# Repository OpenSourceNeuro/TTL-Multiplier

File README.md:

# TTL-Multiplier
a simple rack-mounted hardware to multiple a 5V TTL signal without depleting the current source

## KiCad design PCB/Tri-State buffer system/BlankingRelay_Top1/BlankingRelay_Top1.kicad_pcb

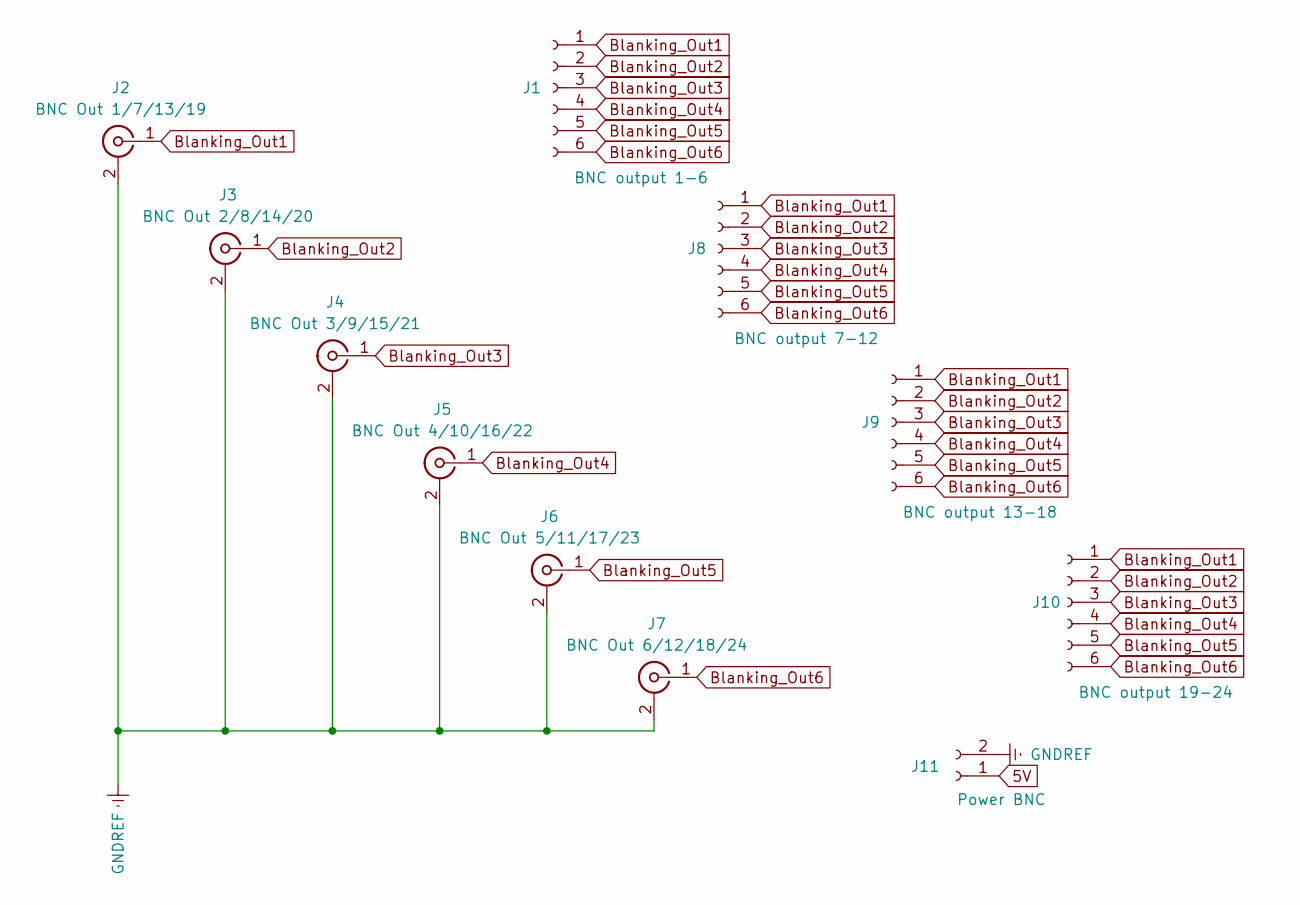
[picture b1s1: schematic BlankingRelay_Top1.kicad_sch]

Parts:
J1: BNC output 1-6; JST_XH_B6B-XH-A_1x06_P2.50mm_Vertical
J2: BNC Out 1/7/13/19; BNC_Socket_TYCO-AMP_LargePads
J3: BNC Out 2/8/14/20; BNC_Socket_TYCO-AMP_LargePads
J4: BNC Out 3/9/15/21; BNC_Socket_TYCO-AMP_LargePads
J5: BNC Out 4/10/16/22; BNC_Socket_TYCO-AMP_LargePads
J6: BNC Out 5/11/17/23; BNC_Socket_TYCO-AMP_LargePads
J7: BNC Out 6/12/18/24; BNC_Socket_TYCO-AMP_LargePads
J8: BNC output 7-12; JST_XH_B6B-XH-A_1x06_P2.50mm_Vertical
J9: BNC output 13-18; JST_XH_B6B-XH-A_1x06_P2.50mm_Vertical
J10: BNC output 19-24; JST_XH_B6B-XH-A_1x06_P2.50mm_Vertical
J11: Power BNC; JST_XH_B2B-XH-A_1x02_P2.50mm_Vertical

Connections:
5V: J11.1
Blanking_Out1: J1.1, J2.1 (In), J8.1, J9.1, J10.1
Blanking_Out2: J1.2, J3.1 (In), J8.2, J9.2, J10.2
Blanking_Out3: J1.3, J4.1 (In), J8.3, J9.3, J10.3
Blanking_Out4: J1.4, J5.1 (In), J8.4, J9.4, J10.4
Blanking_Out5: J1.5, J6.1 (In), J8.5, J9.5, J10.5
Blanking_Out6: J1.6, J7.1 (In), J8.6, J9.6, J10.6
GNDREF: J2.2 (Ext), J3.2 (Ext), J4.2 (Ext), J5.2 (Ext), J6.2 (Ext), J7.2 (Ext), J11.2

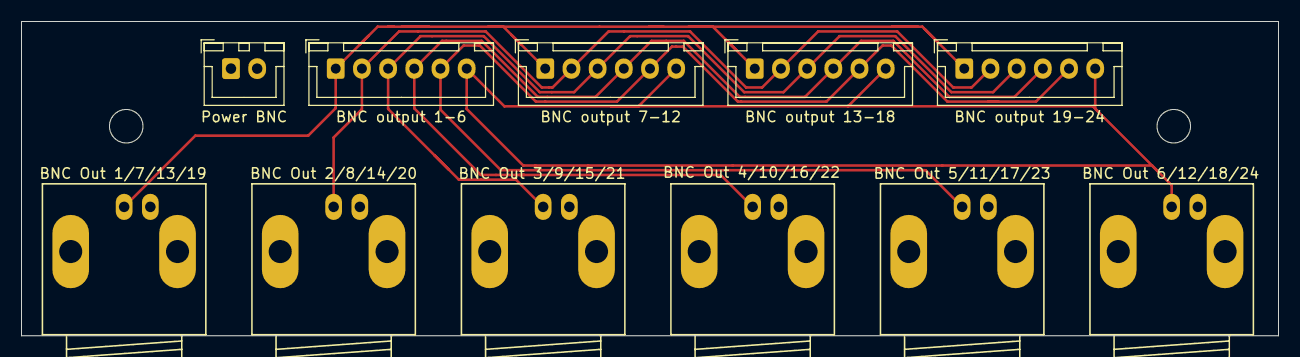
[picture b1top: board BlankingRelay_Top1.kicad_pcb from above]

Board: 2 copper layers, 120.0 x 30.0 mm, 11 parts (0 on the bottom side), 7 nets.

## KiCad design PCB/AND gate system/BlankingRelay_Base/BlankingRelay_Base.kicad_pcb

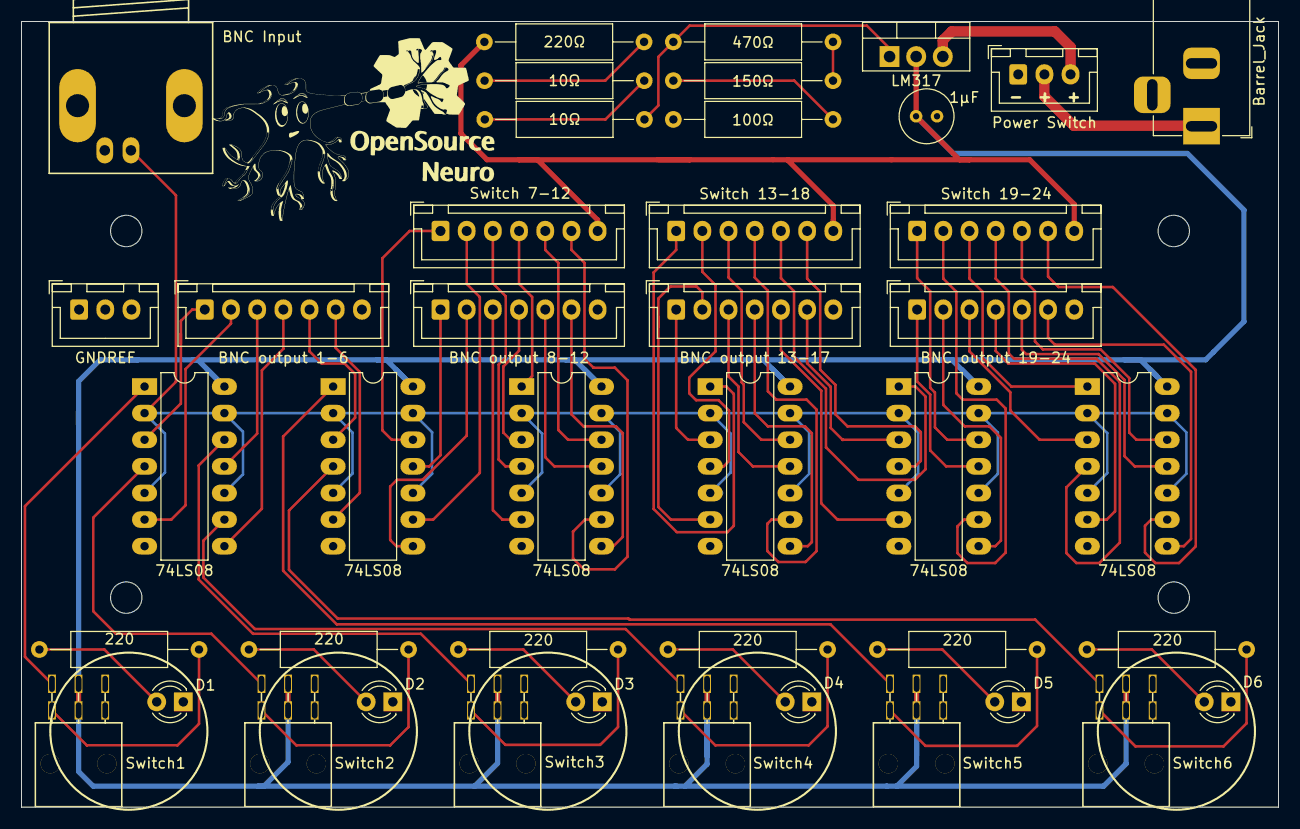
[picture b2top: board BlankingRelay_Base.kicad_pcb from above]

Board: 2 copper layers, 120.0 x 75.0 mm, 47 parts (0 on the bottom side), 70 nets.

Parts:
C1: 1μF; C_Radial_D5.0mm_H5.0mm_P2.00mm
D1, D2, D3, D4, D5, D6: LED; LED_D3.0mm
H1, H2, H3, H4: MountingHole; MountingHole_3mm
J1: Power Switch; JST_XH_B3B-XH-A_1x03_P2.50mm_Vertical
J2: BNC Input; BNC_Socket_TYCO-AMP_LargePads
J3: BNC output 1-6; JST_XH_B7B-XH-A_1x07_P2.50mm_Vertical
J4: BNC output 8-12; JST_XH_B7B-XH-A_1x07_P2.50mm_Vertical
J5: Switch 7-12; JST_XH_B7B-XH-A_1x07_P2.50mm_Vertical
J6: BNC output 13-17; JST_XH_B7B-XH-A_1x07_P2.50mm_Vertical
J7: Switch 13-18; JST_XH_B7B-XH-A_1x07_P2.50mm_Vertical
J8: BNC output 19-24; JST_XH_B7B-XH-A_1x07_P2.50mm_Vertical
J9: Switch 19-24; JST_XH_B7B-XH-A_1x07_P2.50mm_Vertical
J10: Barrel_Jack; BarrelJack_Horizontal
J11: GNDREF; JST_XH_B3B-XH-A_1x03_P2.50mm_Vertical
R1, R2, R3, R4, R5, R6: 220; R_Axial_DIN0309_L9.0mm_D3.2mm_P15.24mm_Horizontal
R7: 470Ω; R_Axial_DIN0309_L9.0mm_D3.2mm_P15.24mm_Horizontal
R8, R10: 10Ω; R_Axial_DIN0309_L9.0mm_D3.2mm_P15.24mm_Horizontal
R9: 150Ω; R_Axial_DIN0309_L9.0mm_D3.2mm_P15.24mm_Horizontal
R11: 100Ω; R_Axial_DIN0309_L9.0mm_D3.2mm_P15.24mm_Horizontal
R12: 220Ω; R_Axial_DIN0309_L9.0mm_D3.2mm_P15.24mm_Horizontal
Switch1, Switch2, Switch3, Switch4, Switch5, Switch6: SW_Push_DPDT; maxi_DPDT_Angled
U1, U2, U3, U4, U5, U6: 74LS08; DIP-14_W7.62mm_LongPads
U7: LM317; TO-220-3_Vertical

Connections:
5V: C1.1, J5.7, J7.7, J9.7, R12.1, Switch1.2 (B), Switch1.5 (B), Switch2.2 (B), Switch2.5 (B), Switch3.2 (B), Switch3.5 (B), Switch4.2 (B), Switch4.5 (B), Switch5.2 (B), Switch5.5 (B), Switch6.2 (B), Switch6.5 (B), U1.14 (VCC), U2.14 (VCC), U3.14 (VCC), U4.14 (VCC), U5.14 (VCC), U6.14 (VCC), U7.2 (VO)
+12V: J1.3, U7.3 (VI)
Blanking_In: J2.1 (In), U1.2, U1.5, U1.10, U1.13, U2.2, U2.5, U2.10, U2.13, U3.2, U3.5, U3.10, U3.13, U4.2, U4.5, U4.10, U4.13, U5.2, U5.5, U5.10, U5.13, U6.2, U6.5, U6.10, U6.13
Blanking_Out1: J3.1, U1.3
Blanking_Out2: J3.2, U1.6
Blanking_Out3: J3.3, U1.11
Blanking_Out4: J3.4, U1.8
Blanking_Out5: J3.5, U2.3
Blanking_Out6: J3.6, U2.6
Blanking_Out7: J4.1, U2.11
Blanking_Out8: J4.2, U2.8
Blanking_Out9: J4.3, U3.6
Blanking_Out10: J4.4, U3.3
Blanking_Out11: J4.5, U3.11
Blanking_Out12: J4.6, U3.8
Blanking_Out13: J6.1, U4.3
Blanking_Out14: J6.2, U4.6
Blanking_Out15: J6.3, U4.11
Blanking_Out16: J6.4, U4.8
Blanking_Out17: J6.6, U5.3
Blanking_Out18: J6.5, U5.6
Blanking_Out19: J8.1, U5.11
Blanking_Out20: J8.2, U5.8
Blanking_Out21: J8.3, U6.3
Blanking_Out22: J8.4, U6.6
Blanking_Out23: J8.5, U6.11
Blanking_Out24: J8.6, U6.8
GNDREF: C1.2, D1.1 (K), D2.1 (K), D3.1 (K), D4.1 (K), D5.1 (K), D6.1 (K), J1.1, J2.2 (Ext), J3.7, J4.7, J6.7, J8.7, J10.2, J11.1, J11.2, J11.3, R11.1, U1.7 (GND), U2.7 (GND), U3.7 (GND), U4.7 (GND), U5.7 (GND), U6.7 (GND)
unnamed: D1.2 (A), R1.2
unnamed: D2.2 (A), R2.2
unnamed: D3.2 (A), R3.2
unnamed: D4.2 (A), R4.2
unnamed: D5.2 (A), R5.2
unnamed: D6.2 (A), R6.2
unnamed: J1.2, J10.1
unnamed: R1.1, Switch1.4 (A)
unnamed: R2.1, Switch2.4 (A)
unnamed: R3.1, Switch3.4 (A)
unnamed: R4.1, Switch4.4 (A)
unnamed: R5.1, Switch5.4 (A)
unnamed: R6.1, Switch6.4 (A)
unnamed: R7.2, R9.2
unnamed: R10.1, R12.2
unnamed: R8.1, R10.2
unnamed: R9.1, R11.2
unnamed: R7.1, R8.2, U7.1 (ADJ)
On_1: Switch1.1 (A), U1.1
On_2: Switch2.1 (A), U1.4
On_3: Switch3.1 (A), U1.12
On_4: Switch4.1 (A), U1.9
On_5: Switch5.1 (A), U2.1
On_6: Switch6.1 (A), U2.4
On_7: J5.1, U2.12
On_8: J5.2, U2.9
On_9: J5.3, U3.4
On_10: J5.4, U3.1
On_11: J5.5, U3.12
On_12: J5.6, U3.9
On_13: J7.1, U4.1
On_14: J7.2, U4.4
On_15: J7.3, U4.12
On_16: J7.4, U4.9
On_17: J7.5, U5.1
On_18: J7.6, U5.4
On_19: J9.1, U5.12
On_20: J9.2, U5.9
On_21: J9.3, U6.1
On_22: J9.4, U6.4
On_23: J9.5, U6.12
On_24: J9.6, U6.9

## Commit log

2024-02-13 Tri-State Buffer system first commit
2024-05-16 Started wish-list/notes for next iteration
